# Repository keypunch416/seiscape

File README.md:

# seiscape
Beaglebone cape with 24-bit sigma-delta A/D, TCXO, and split power supplies for a Yuma force-balance vertical seismometer

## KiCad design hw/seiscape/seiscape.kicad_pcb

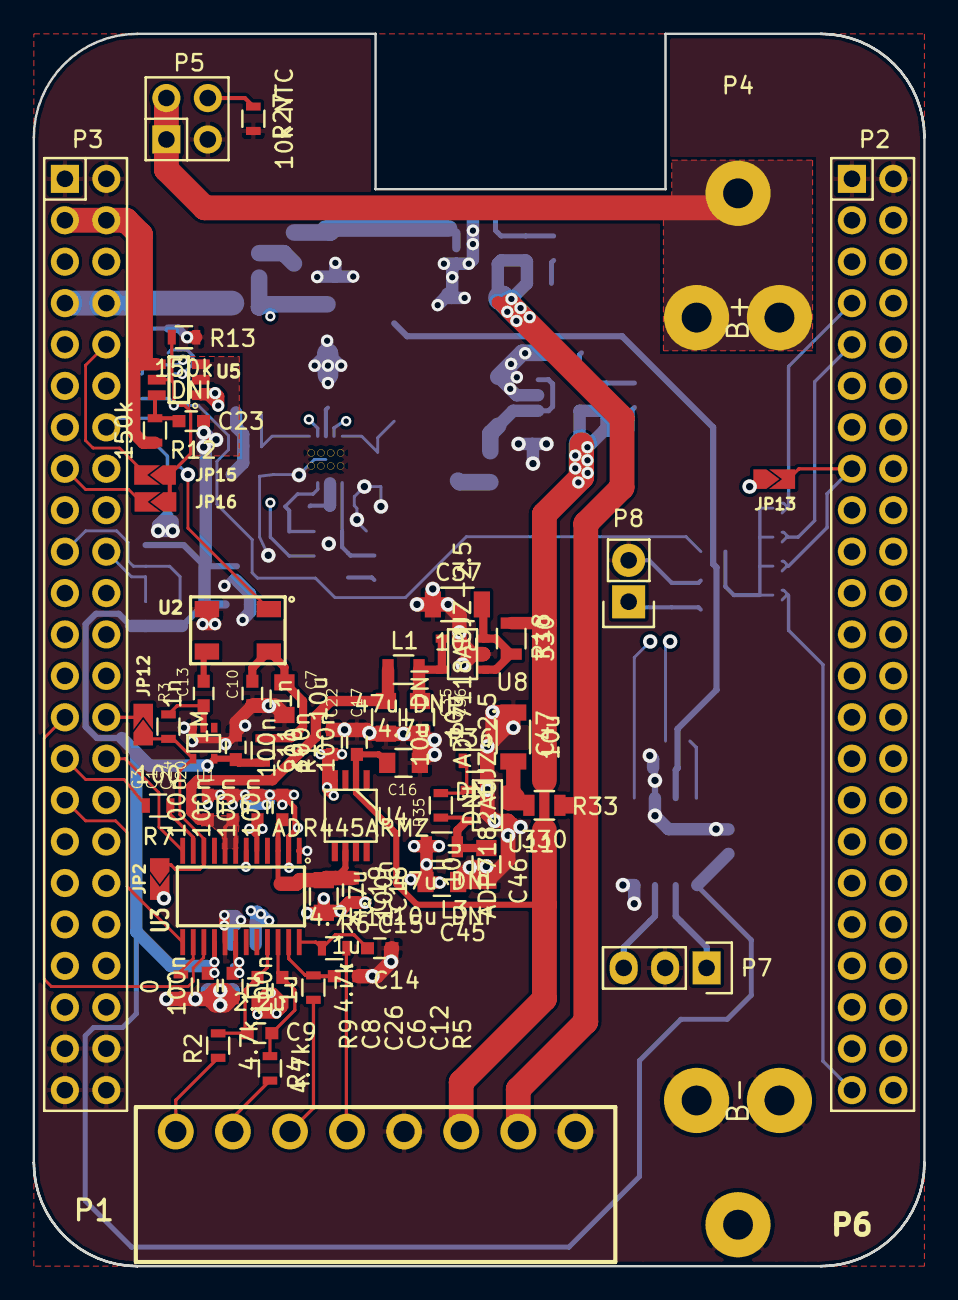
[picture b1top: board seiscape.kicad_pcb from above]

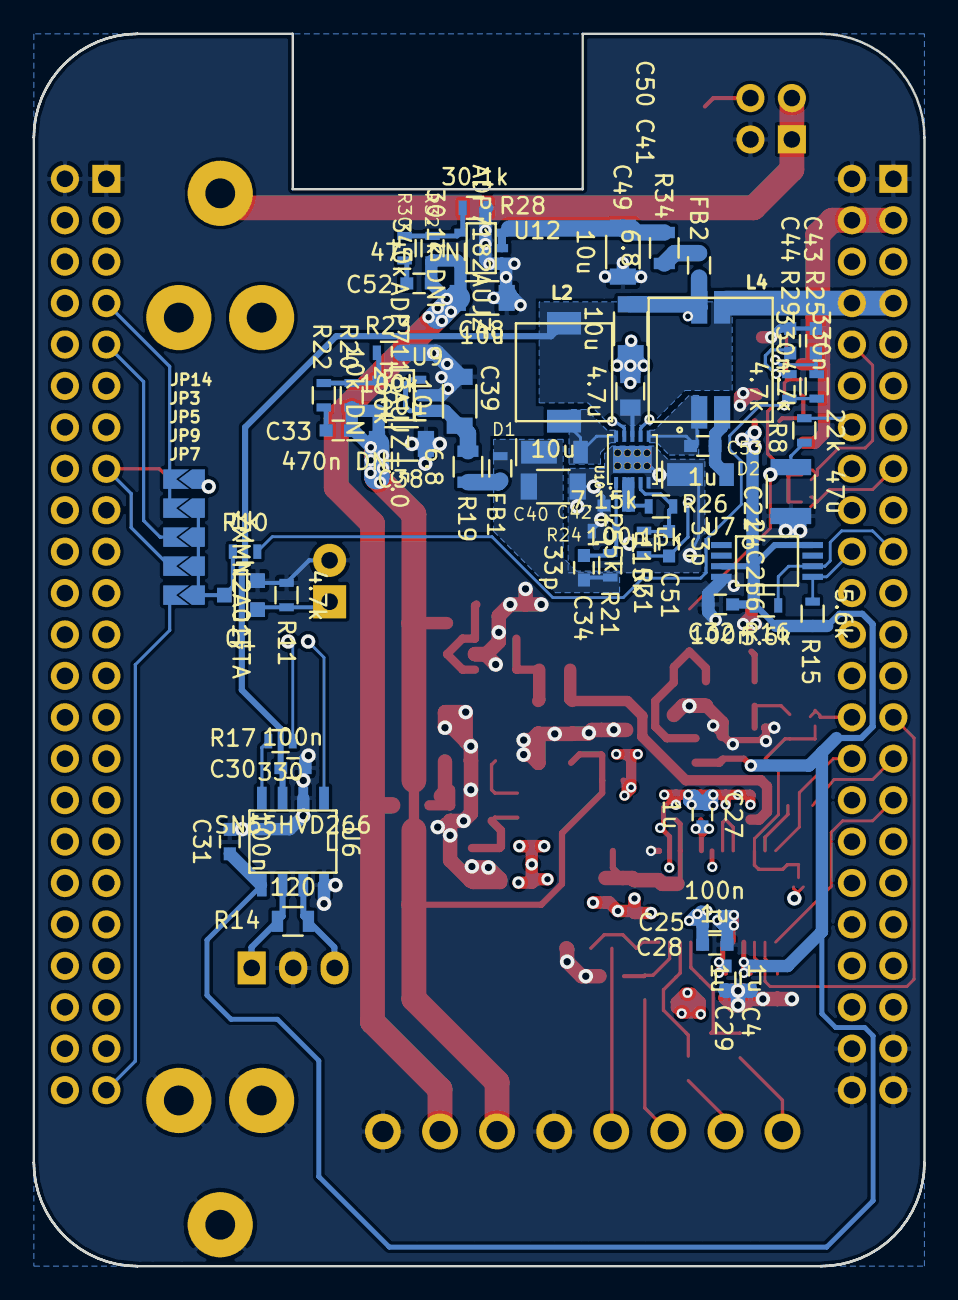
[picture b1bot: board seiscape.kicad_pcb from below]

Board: 4 copper layers, 54.6 x 75.6 mm, 126 parts (62 on the bottom side), 75 nets.

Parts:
C1, C3, C8, C11, C17, C18, C20, C22, C24, C25, C26, C30, C31, C32, C42: 100n; C_0603
C4, C6, C12, C14, C15, C27, C28, C29, C53: 1u; C_0603
C7, C36, C46: 10u; C_0805
C9: 2.2u; C_0603
C10, C13: 1n; C_0603
C16, C19, C41: 4.7u; C_0805
C21: 47u; C_1210
C23: DNI; C_0603
C33: 470n DNI; C_0603
C34, C51: 33p; C_0603
C35, C45: 10u DNI; C_0805
C37, C38, C39, C40, C47, C48, C49, C50: 10u; C_1206
C43, C44: 330n; C_0603
C52: 47n DNI; C_0603
D1, D2: DFLS130L; PowerDI123
FB1, FB2: MMZ1608B102CTA00; R_0603
JP2, JP3, JP5, JP7, JP9, JP12, JP13, JP14, JP15, JP16: JUMPER; Solder_Bridge
L1, L3: 47u DNI; R_0805
L2: 10u; Sumida_CDRG5D28RHP
L4: 10u; Eaton_DRQ74
P1: Combicon MC 3.5mm; COMBICON_MC_3p50_1x08
P2: BBB-P8; Pin_Header_Straight_2x23
P3: BBB-P9; Pin_Header_Straight_2x23
P4: B+; Keystone54_BattClip
P5: BBB TP5/6/7/8; Pin_Header_Straight_2x02
P6: B-; Keystone54_BattClip
P7: CAN; Pin_Header_Straight_1x03
P8: GPS timepulse; Pin_Header_Straight_1x02
Q1: ZXMN2A01FTA; SOT-23-GDS
R1: 200; R_0603
R2, R4, R5, R6, R11, R25, R29: 4.7k; R_0603
R3: 1M; R_0603
R7: 100; R_0603
R8: 22k; R_0603
R9: 0; R_0603
R10: 1k; R_0603
R12, R13: 150k; R_0603
R14: 120; R_0805
R15, R16: 5.6k; R_0603
R17: 330; R_0603
R18, R33: 330; R_0805
R19, R34: 6.8; R_0805
R20: 200k; R_0603
R21: 115k; R_0603
R22: 10k DNI; R_0603
R23: 100k; R_0603
R24: 7.15k; R_0603
R26: 15k; R_0603
R27: 10k NTC; R_0603
R28: 30.1k; R_0603
R30: 30.1k DNI; R_0603
R31: 255k; R_0603
R32: 340k; R_0603
R35, R36: DNI; R_0603
U1: NC7SZ04-P5X; SC70
U2: ASVTX-09-14.4MHZ; Abracon_ASVTX09
U3: AD7175-2; TSSOP24
U4: ADR445ARMZ; MSOP-8
U5: TPS27082L-DDC; TI_DDC_6
U6: SN65HVD266; SOIC-8-W
U7: 24C256; TSSOP8
U8: ADP7118AUJZ-2.5; SOT-23-5
U9: ADP7118AUJZ-5.0; SOT-23-5
U10: LT3471; DFN10_thermal
U11: ADP7182AUJZ-2.5; SOT-23-5
U12: ADP7182AUJZ; SOT-23-5

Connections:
+2.5V: C1.2, C3.2, C35.2, L1.1, U3.7, U3.8
+3.3V: C4.1, C8.1, C11.1, C23.1, C31.1, C32.2, R1.1, R15.1, R16.1, U1.5, U3.16, U5.2, U5.3, U6.5, U7.3, U7.8
+5V: C30.2, C41.2, L2.2, L4.3, P3.7, P3.8, U6.3, U10.8
+15V: C16.2, C17.2, C33.2, C38.2, P1.3, R18.2, R20.1, U4.2, U9.5
-15V: C48.1, C52.1, P1.2, R32.2, R33.2, U12.5
/BAT: P4.1, P5.1, P5.2
/TS: P5.4, R27.2
AVSS: C1.1, C3.1, C6.1, C12.2, C18.1, C19.1, C20.1, C22.2, C24.1, C25.2, C27.1, C28.2, C45.1, L3.1, U3.2, U3.6, U4.4
GND: C4.2, C7.1, C8.2, C10.1, C11.2, C14.1, C15.1, C16.1, C17.1, C21.1, C22.1, C25.1, C26.1, C28.1, C29.1, C30.1, C31.2, C32.1, C35.1, C36.1, C37.1, C38.1, C39.1, C40.1, C41.1, C42.1, C43.1, C44.2, C45.2, C46.2, C47.2, C48.2, C49.2, C50.2, D2.2, P1.1, P1.4, P2.1, P2.2, P3.1, P3.2, P3.43, P3.44, P3.45, P3.46, P5.3, P6.1, P7.2, P8.2, Q1.S, R9.2, R11.2, R13.2, R23.2, R24.2, R27.1, R28.1, R36.2, U1.3, U2.2, U3.1, U3.17, U5.1, U6.2, U6.8, U7.4, U8.2, U9.2, U10.5, U10.11, U11.1, U12.1
unnamed: C6.2, C9.2, R2.2, U3.21
unnamed: C7.2, C10.2, R1.2, U2.4
unnamed: C9.1, C12.1, R4.2, U3.22
unnamed: C13.1, U2.3
unnamed: C13.2, R3.2, U1.2
unnamed: C14.2, R5.2, U3.23
unnamed: C15.2, R6.2, U3.24
unnamed: C18.2, C19.2, C20.2, U3.3, U4.6
unnamed: C21.2, R8.1, U2.1
unnamed: C23.2, R12.1, U5.6
unnamed: C24.2, C27.2, U3.5
unnamed: C26.2, C29.2, U3.18
unnamed: C33.1, R22.1
unnamed: C34.1, R21.2, R24.1, U10.1
unnamed: C34.2, C40.2, D1.2, FB1.2, R21.1
unnamed: C36.2, L1.2, U8.4, U8.5
unnamed: C37.2, R18.1, U8.1, U8.3
unnamed: C39.2, R19.1, U9.1, U9.3
unnamed: C42.2, R26.1, U10.2, U10.3
unnamed: C43.2, R25.1, U10.9
unnamed: C44.1, R29.1, U10.7
unnamed: C46.1, L3.2, R35.1, U11.5
unnamed: C47.1, R33.1, U11.2, U11.3
unnamed: C49.1, R34.1, U12.2, U12.3
unnamed: C50.1, C51.1, FB2.2, L4.4, R31.2
unnamed: C51.2, R26.2, R31.1, U10.4
unnamed: C52.2, R30.1
unnamed: C53.1, L4.1, U10.6
unnamed: C53.2, D2.1, L4.2
unnamed: D1.1, L2.1, U10.10
unnamed: FB1.1, R19.2
unnamed: FB2.1, R34.2
unnamed: JP3.1, JP5.1, JP7.1, JP9.1, Q1.D, R10.2
unnamed: JP2.1, JP12.1, R3.1, U1.4, U3.10
unnamed: JP13.1, JP14.1, P3.29, R7.2
unnamed: JP15.2, P3.10
unnamed: JP16.2, P3.15
unnamed: P1.5, R6.1
unnamed: P1.6, R5.1
unnamed: P1.7, R4.1
unnamed: P1.8, R2.1
unnamed: P3.3, P3.4, R12.2, U5.4
unnamed: P3.14, R8.2
unnamed: P3.19, R16.2, U7.6
unnamed: P3.20, R15.2, U7.5
unnamed: P3.27, U3.15
unnamed: P3.30, U3.12
unnamed: P3.31, U3.13
unnamed: P7.1, R14.2, U6.6
unnamed: P7.3, R14.1, U6.7
unnamed: P8.1, Q1.G, R11.1
unnamed: R7.1, U3.11
unnamed: R9.1, U3.14
unnamed: R17.1, U6.4
unnamed: R20.2, R22.2, R23.1, U9.4
unnamed: R28.2, R30.2, R32.1, U12.4
unnamed: R35.2, R36.1, U11.4
cape_en: JP15.1, JP16.1, R10.1, R13.1, R25.2, R29.2, U5.5
dcan1_rx: P3.24, R17.2
dcan1_tx: P3.26, U6.1
pru0_3: JP12.2, P3.28
pru1_0: JP7.2, P2.45
pru_ecap0: JP9.2, JP13.2, P2.15
tclkin: JP2.2, P3.41
timer4: JP3.2, JP14.2, P2.7
timer5: JP5.2, P2.9

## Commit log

2016-02-14 Acquire blocks of SAMPLES_PER_BLOCK forever, in circular buffer
2016-02-14 Add hardware files
2016-02-15 First working code
